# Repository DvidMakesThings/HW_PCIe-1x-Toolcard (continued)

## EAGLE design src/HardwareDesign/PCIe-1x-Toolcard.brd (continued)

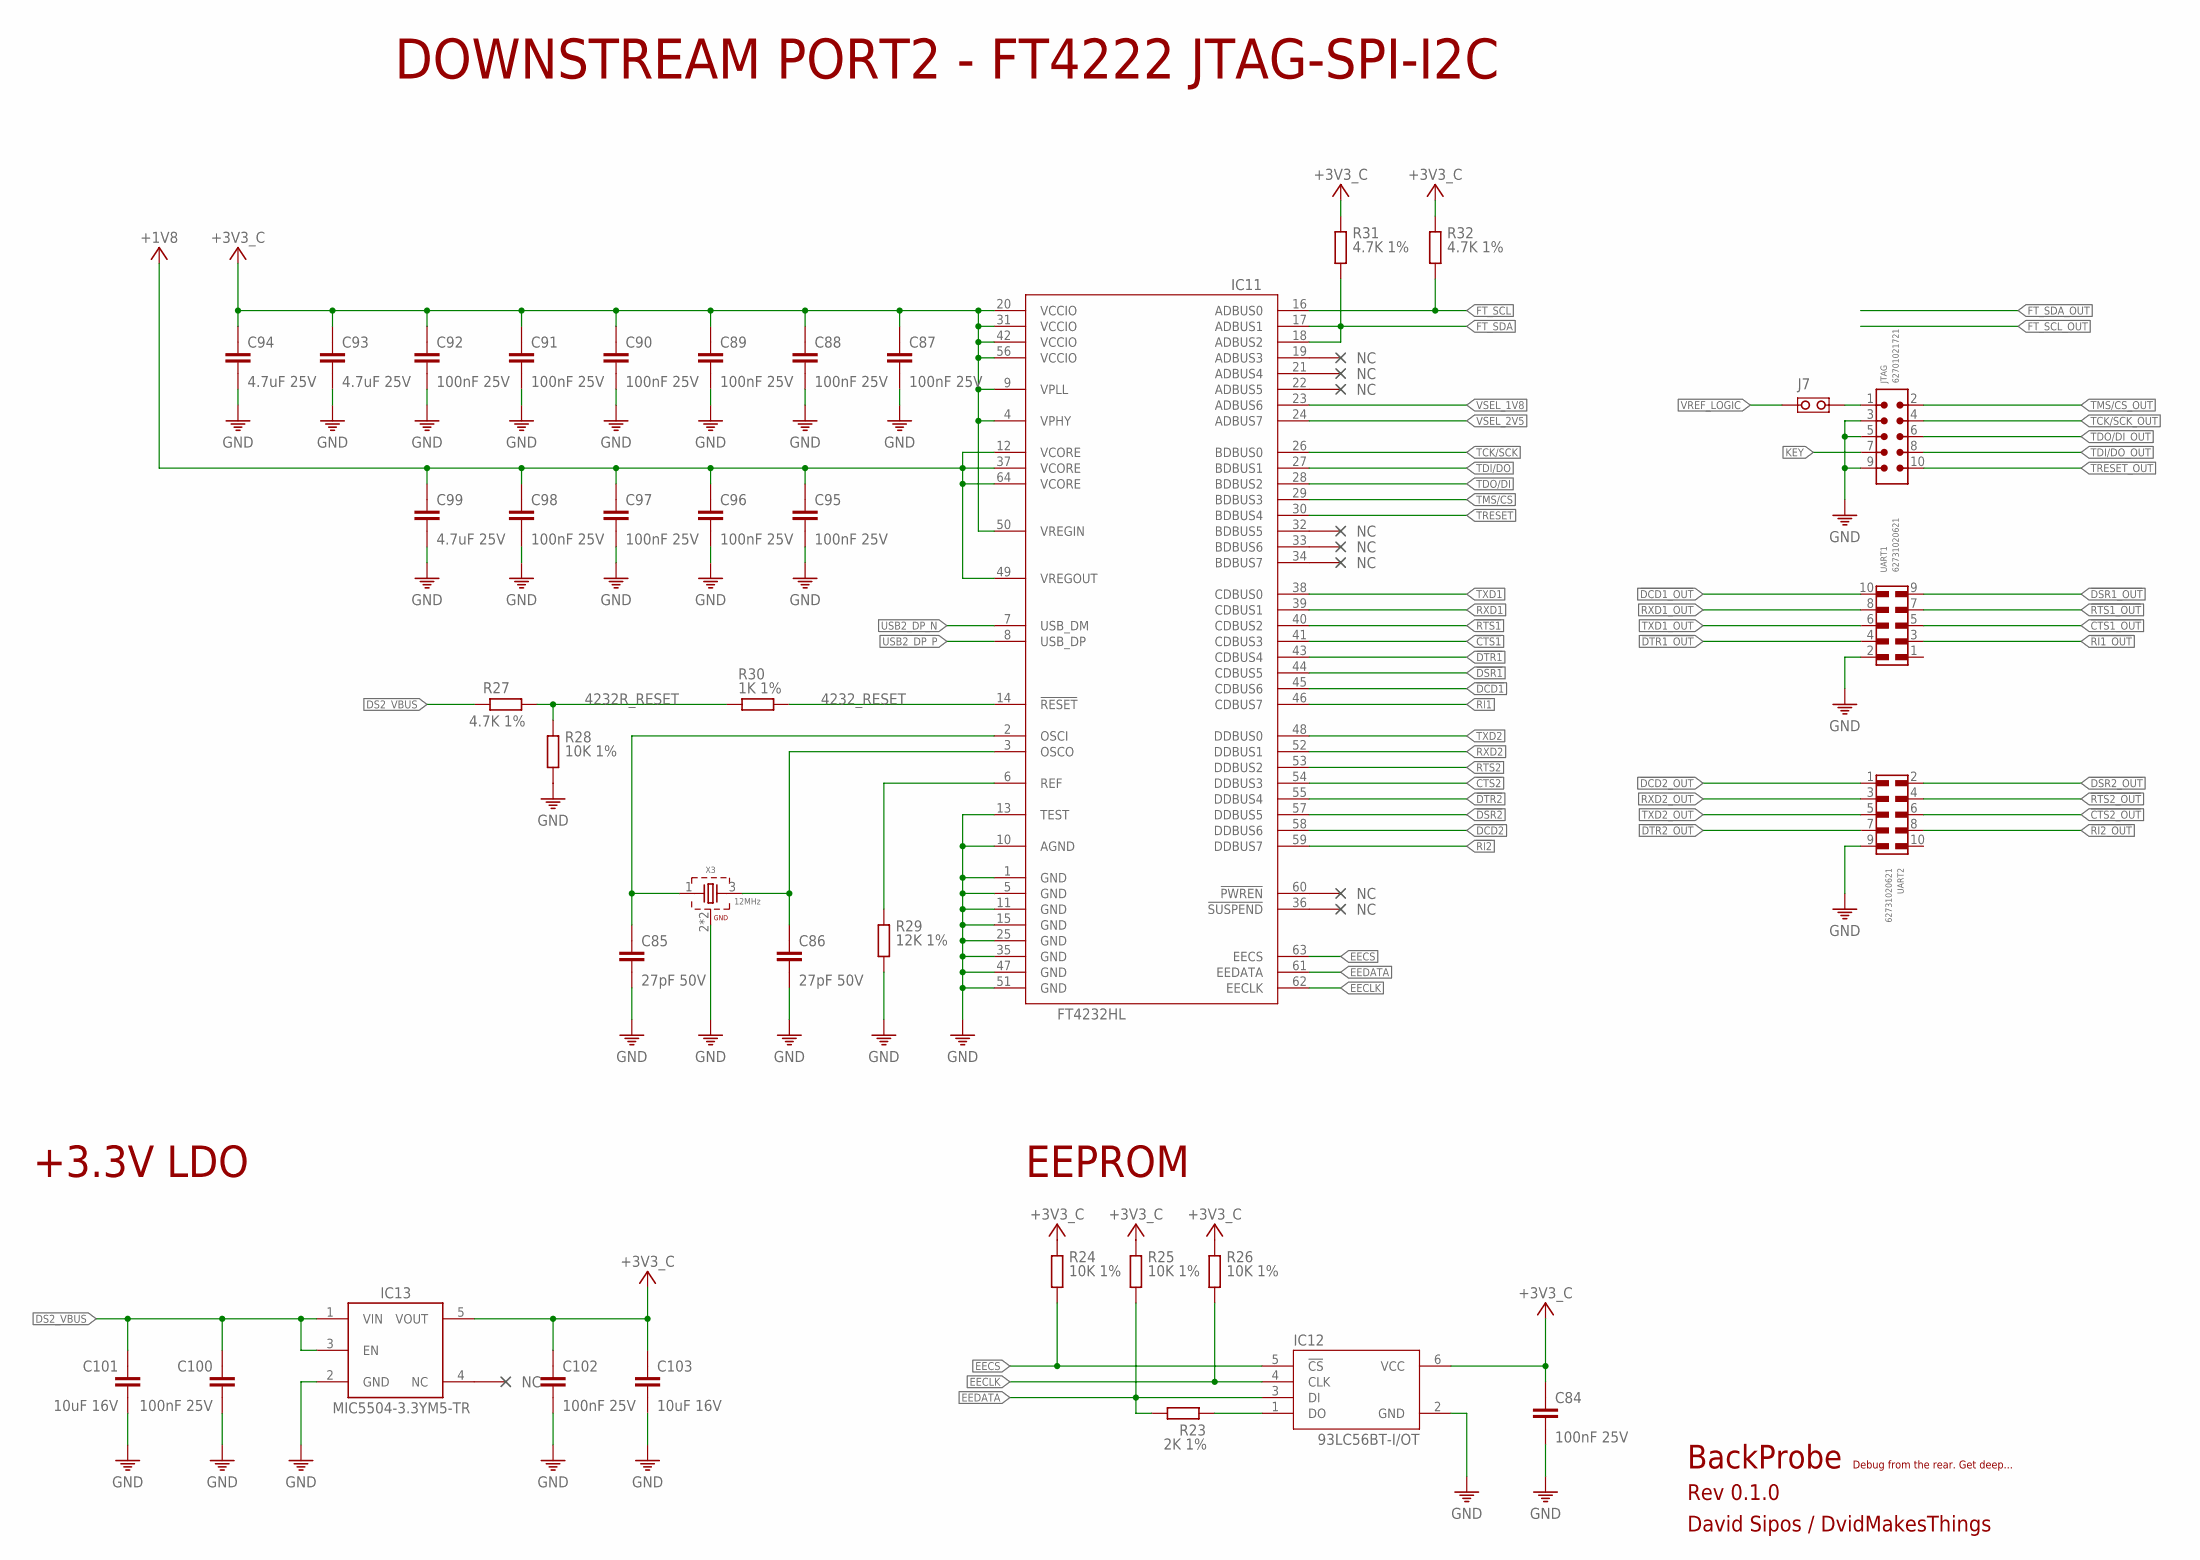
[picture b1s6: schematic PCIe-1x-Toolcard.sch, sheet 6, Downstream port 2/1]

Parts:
C84: 100nF 25V; 0402
C85, C86: 27pF 50V; 0201
C87, C88, C89, C90, C91, C92, C95, C96, C97, C98, C100, C102: 100nF 25V; 0201
C93, C94, C99: 4.7uF 25V; 0402
C101, C103: 10uF 16V; 0603
IC11: FT4232HL; LQFP64-10X10
IC12: 93LC56BT-I/OT; SOT95P280X145-6N
IC13: MIC5504-3.3YM5; SOT23-5
J7: JUMPER-NO; J-0402-NO
JTAG: 62701021721
R23: 2K 1%; 0201
R24, R25, R26, R28: 10K 1%; 0201
R27, R31, R32: 4.7K 1%; 0201
R29: 12K 1%; 0201
R30: 1K 1%; 0201
UART1, UART2: 62731020621
X3: 12MHz; WE-XTAL_CFPX-180

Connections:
4232R_RESET: R27.2, R28.1, R30.1
4232_RESET: IC11.14 (!RESET), R30.2
!CTS1: IC11.41 (CDBUS3); also elsewhere on the board
!CTS1_OUT: UART1.5; also elsewhere on the board
!CTS2: IC11.54 (DDBUS3); also elsewhere on the board
!CTS2_OUT: UART2.6; also elsewhere on the board
!DCD1: IC11.45 (CDBUS6); also elsewhere on the board
!DCD1_OUT: UART1.10; also elsewhere on the board
!DCD2: IC11.58 (DDBUS6); also elsewhere on the board
!DCD2_OUT: UART2.1; also elsewhere on the board
!DSR1: IC11.44 (CDBUS5); also elsewhere on the board
!DSR1_OUT: UART1.9; also elsewhere on the board
!DSR2: IC11.57 (DDBUS5); also elsewhere on the board
!DSR2_OUT: UART2.2; also elsewhere on the board
!DTR1: IC11.43 (CDBUS4); also elsewhere on the board
!DTR1_OUT: UART1.4; also elsewhere on the board
!DTR2: IC11.55 (DDBUS4); also elsewhere on the board
!DTR2_OUT: UART2.7; also elsewhere on the board
!RI1: IC11.46 (CDBUS7); also elsewhere on the board
!RI1_OUT: UART1.3; also elsewhere on the board
!RI2: IC11.59 (DDBUS7); also elsewhere on the board
!RI2_OUT: UART2.8; also elsewhere on the board
!RTS1: IC11.40 (CDBUS2); also elsewhere on the board
!RTS1_OUT: UART1.7; also elsewhere on the board
!RTS2: IC11.53 (DDBUS2); also elsewhere on the board
!RTS2_OUT: UART2.4; also elsewhere on the board
+1V8: C95.1, C96.1, C97.1, C98.1, C99.1, IC11.12 (VCORE), IC11.37 (VCORE), IC11.49 (VREGOUT), IC11.64 (VCORE)
+3V3C: C84.1, C87.1, C88.1, C89.1, C90.1, C91.1, C92.1, C93.1, C94.1, C102.1, C103.1, IC11.4 (VPHY), IC11.9 (VPLL), IC11.20 (VCCIO), IC11.31 (VCCIO), IC11.42 (VCCIO), IC11.50 (VREGIN), IC11.56 (VCCIO), IC12.6 (VCC), IC13.5 (VOUT), R24.1, R25.1, R26.1, R31.1, R32.1; also elsewhere on the board
DS2_VBUS: C100.1, C101.1, IC13.1 (VIN), IC13.3 (EN), R27.1; also elsewhere on the board
EECLK: IC11.62 (EECLK), IC12.4 (CLK), R26.2
EECS: IC11.63 (EECS), IC12.5 (!CS), R24.2
EEDATA: IC11.61 (EEDATA), IC12.3 (DI), R23.2, R25.2
FT_SCL: IC11.16 (ADBUS0), R32.2; also elsewhere on the board
FT_SDA: IC11.17 (ADBUS1), IC11.18 (ADBUS2), R31.2; also elsewhere on the board
GND: C84.2, C85.2, C86.2, C87.2, C88.2, C89.2, C90.2, C91.2, C92.2, C93.2, C94.2, C95.2, C96.2, C97.2, C98.2, C99.2, C100.2, C101.2, C102.2, C103.2, IC11.1 (GND), IC11.5 (GND), IC11.10 (AGND), IC11.11 (GND), IC11.13 (TEST), IC11.15 (GND), IC11.25 (GND), IC11.35 (GND), IC11.47 (GND), IC11.51 (GND), IC12.2 (GND), IC13.2 (GND), JTAG.3, JTAG.5, JTAG.9, R28.2, R29.2, UART1.2, UART2.9, X3.2 (GND), X3.4 (GND); also elsewhere on the board
KEY: JTAG.7
unnamed: IC11.6 (REF), R29.1
unnamed: C85.1, IC11.2 (OSCI), X3.1
unnamed: IC12.1 (DO), R23.1
unnamed: C86.1, IC11.3 (OSCO), X3.3 (2)
unnamed: J7.2, JTAG.1
RXD1: IC11.39 (CDBUS1); also elsewhere on the board
RXD1_OUT: UART1.8; also elsewhere on the board
RXD2: IC11.52 (DDBUS1); also elsewhere on the board
RXD2_OUT: UART2.3; also elsewhere on the board
TCK/SCK: IC11.26 (BDBUS0); also elsewhere on the board
TCK/SCK_OUT: JTAG.4; also elsewhere on the board
TDI/DO: IC11.27 (BDBUS1); also elsewhere on the board
TDI/DO_OUT: JTAG.8; also elsewhere on the board
TDO/DI: IC11.28 (BDBUS2); also elsewhere on the board
TDO/DI_OUT: JTAG.6; also elsewhere on the board
TMS/CS: IC11.29 (BDBUS3); also elsewhere on the board
TMS/CS_OUT: JTAG.2; also elsewhere on the board
TRESET: IC11.30 (BDBUS4)
TRESET_OUT: JTAG.10
TXD1: IC11.38 (CDBUS0); also elsewhere on the board
TXD1_OUT: UART1.6; also elsewhere on the board
TXD2: IC11.48 (DDBUS0); also elsewhere on the board
TXD2_OUT: UART2.5; also elsewhere on the board
USB2_DP_N: IC11.7 (USB_DM); also elsewhere on the board
USB2_DP_P: IC11.8 (USB_DP); also elsewhere on the board
VREF_LOGIC: J7.1; also elsewhere on the board
VSEL_1V8: IC11.23 (ADBUS6); also elsewhere on the board
VSEL_2V5: IC11.24 (ADBUS7); also elsewhere on the board

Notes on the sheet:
BackProbe
Rev 0.1.0
David Sipos / DvidMakesThings
Debug from the rear. Get deep...
DOWNSTREAM PORT2 - FT4222 JTAG-SPI-I2C
+3.3V LDO
EEPROM

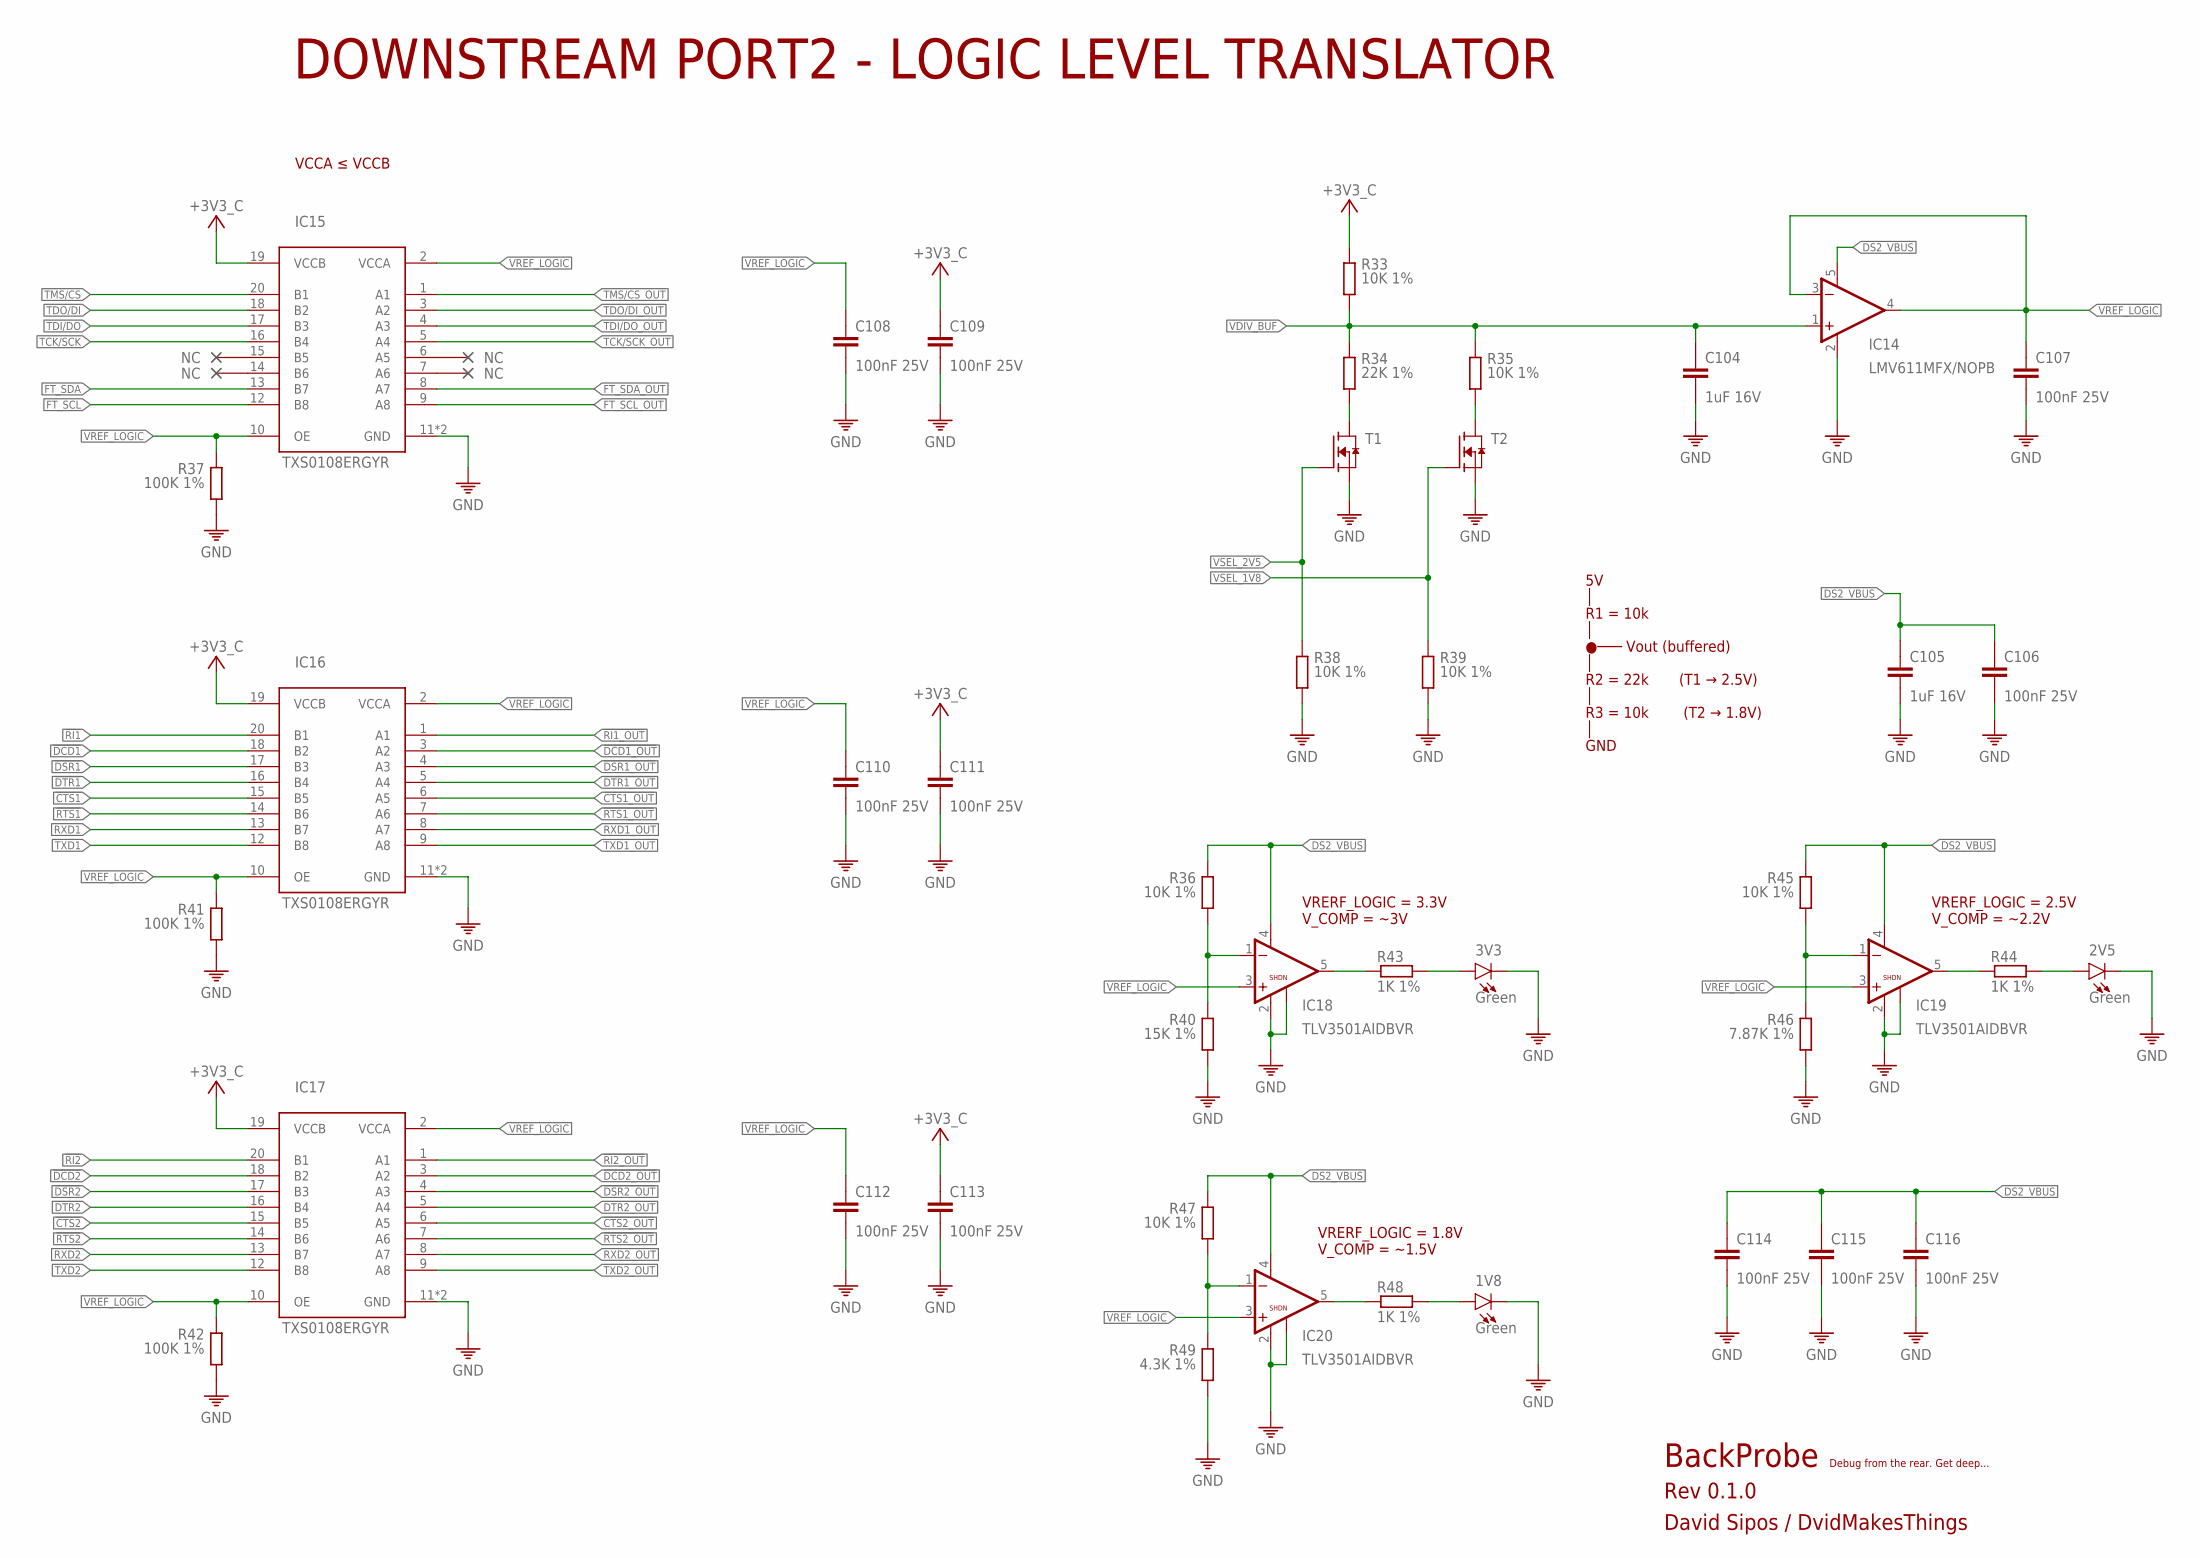
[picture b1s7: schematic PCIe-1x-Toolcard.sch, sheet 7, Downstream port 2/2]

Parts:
1V8, 2V5, 3V3: Green; LED-0603
C104, C105: 1uF 16V; 0201
C106, C107, C108, C109, C110, C111, C112, C113, C114, C115, C116: 100nF 25V; 0201
IC14: LMV611MFX/NOPB; SOT23-5
IC15, IC16, IC17: TXS0108ERGYR; VQFN24
IC18, IC19, IC20: TLV3501AIDBVR; SOT95P280X145-6N
R33, R35, R38, R39: 10K 1%; 0402
R34: 22K 1%; 0402
R36, R45, R47: 10K 1%; 0201
R37, R41, R42: 100K 1%; 0201
R40: 15K 1%; 0201
R43, R44, R48: 1K 1%; 0603
R46: 7.87K 1%; 0201
R49: 4.3K 1%; 0201
T1, T2: BSS138; SOT23

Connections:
!CTS1: IC16.15 (B5); also elsewhere on the board
!CTS1_OUT: IC16.6 (A5); also elsewhere on the board
!CTS2: IC17.15 (B5); also elsewhere on the board
!CTS2_OUT: IC17.6 (A5); also elsewhere on the board
!DCD1: IC16.18 (B2); also elsewhere on the board
!DCD1_OUT: IC16.3 (A2); also elsewhere on the board
!DCD2: IC17.18 (B2); also elsewhere on the board
!DCD2_OUT: IC17.3 (A2); also elsewhere on the board
!DSR1: IC16.17 (B3); also elsewhere on the board
!DSR1_OUT: IC16.4 (A3); also elsewhere on the board
!DSR2: IC17.17 (B3); also elsewhere on the board
!DSR2_OUT: IC17.4 (A3); also elsewhere on the board
!DTR1: IC16.16 (B4); also elsewhere on the board
!DTR1_OUT: IC16.5 (A4); also elsewhere on the board
!DTR2: IC17.16 (B4); also elsewhere on the board
!DTR2_OUT: IC17.5 (A4); also elsewhere on the board
!RI1: IC16.20 (B1); also elsewhere on the board
!RI1_OUT: IC16.1 (A1); also elsewhere on the board
!RI2: IC17.20 (B1); also elsewhere on the board
!RI2_OUT: IC17.1 (A1); also elsewhere on the board
!RTS1: IC16.14 (B6); also elsewhere on the board
!RTS1_OUT: IC16.7 (A6); also elsewhere on the board
!RTS2: IC17.14 (B6); also elsewhere on the board
!RTS2_OUT: IC17.7 (A6); also elsewhere on the board
+3V3C: C109.1, C111.1, C113.1, IC15.19 (VCCB), IC16.19 (VCCB), IC17.19 (VCCB), R33.1; also elsewhere on the board
COMP18_O: IC20.5 (OUT), R48.1
COMP25_O: IC19.5 (OUT), R44.1
COMP33_O: IC18.5 (OUT), R43.1
D25: R35.2, T2.3 (D)
D33: R34.2, T1.3 (D)
DS2_VBUS: C105.1, C106.1, C114.1, C115.1, C116.1, IC14.5 (V+), IC18.4 (V+), IC19.4 (V+), IC20.4 (V+), R36.1, R45.1, R47.1; also elsewhere on the board
FT_SCL: IC15.12 (B8); also elsewhere on the board
FT_SCL_OUT: IC15.9 (A8)
FT_SDA: IC15.13 (B7); also elsewhere on the board
FT_SDA_OUT: IC15.8 (A7)
GND: 1V8.C, 2V5.C, 3V3.C, C104.2, C105.2, C106.2, C107.2, C108.2, C109.2, C110.2, C111.2, C112.2, C113.2, C114.2, C115.2, C116.2, IC14.2 (V-), IC15.11 (GND), IC15.PAD (GND), IC16.11 (GND), IC16.PAD (GND), IC17.11 (GND), IC17.PAD (GND), IC18.2 (V-), IC18.6 (SHDN), IC19.2 (V-), IC19.6 (SHDN), IC20.2 (V-), IC20.6 (SHDN), R37.2, R38.2, R39.2, R40.2, R41.2, R42.2, R46.2, R49.2, T1.2 (S), T2.2 (S); also elsewhere on the board
unnamed: 3V3.A, R43.2
unnamed: 2V5.A, R44.2
unnamed: 1V8.A, R48.2
RXD1: IC16.13 (B7); also elsewhere on the board
RXD1_OUT: IC16.8 (A7); also elsewhere on the board
RXD2: IC17.13 (B7); also elsewhere on the board
RXD2_OUT: IC17.8 (A7); also elsewhere on the board
TCK/SCK: IC15.16 (B4); also elsewhere on the board
TCK/SCK_OUT: IC15.5 (A4); also elsewhere on the board
TDI/DO: IC15.17 (B3); also elsewhere on the board
TDI/DO_OUT: IC15.4 (A3); also elsewhere on the board
TDO/DI: IC15.18 (B2); also elsewhere on the board
TDO/DI_OUT: IC15.3 (A2); also elsewhere on the board
TMS/CS: IC15.20 (B1); also elsewhere on the board
TMS/CS_OUT: IC15.1 (A1); also elsewhere on the board
TXD1: IC16.12 (B8); also elsewhere on the board
TXD1_OUT: IC16.9 (A8); also elsewhere on the board
TXD2: IC17.12 (B8); also elsewhere on the board
TXD2_OUT: IC17.9 (A8); also elsewhere on the board
VDIV_BUF: C104.1, IC14.1 (+IN), R33.2, R34.1, R35.1
VREF_LOGIC: C107.1, C108.1, C110.1, C112.1, IC14.3 (-IN), IC14.4 (OUT), IC15.2 (VCCA), IC15.10 (OE), IC16.2 (VCCA), IC16.10 (OE), IC17.2 (VCCA), IC17.10 (OE), IC18.3 (+IN), IC19.3 (+IN), IC20.3 (+IN), R37.1, R41.1, R42.1; also elsewhere on the board
VSEL_1V8: R39.1, T2.1 (G); also elsewhere on the board
VSEL_2V5: R38.1, T1.1 (G); also elsewhere on the board
V_COMP18: IC20.1 (-IN), R47.2, R49.1
V_COMP25: IC19.1 (-IN), R45.2, R46.1
V_COMP33: IC18.1 (-IN), R36.2, R40.1

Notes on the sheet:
BackProbe
Rev 0.1.0
David Sipos / DvidMakesThings
Debug from the rear. Get deep...
DOWNSTREAM PORT2 - LOGIC LEVEL TRANSLATOR
5V │ R1 = 10k │ ●─── Vout (buffered) │ R2 = 22k (T1 → 2.5V) │ R3 = 10k (T2 → 1.8V) │ GND
VCCA ≤ VCCB
VRERF_LOGIC = 3.3V V_COMP = ~3V
VRERF_LOGIC = 2.5V V_COMP = ~2.2V
VRERF_LOGIC = 1.8V V_COMP = ~1.5V

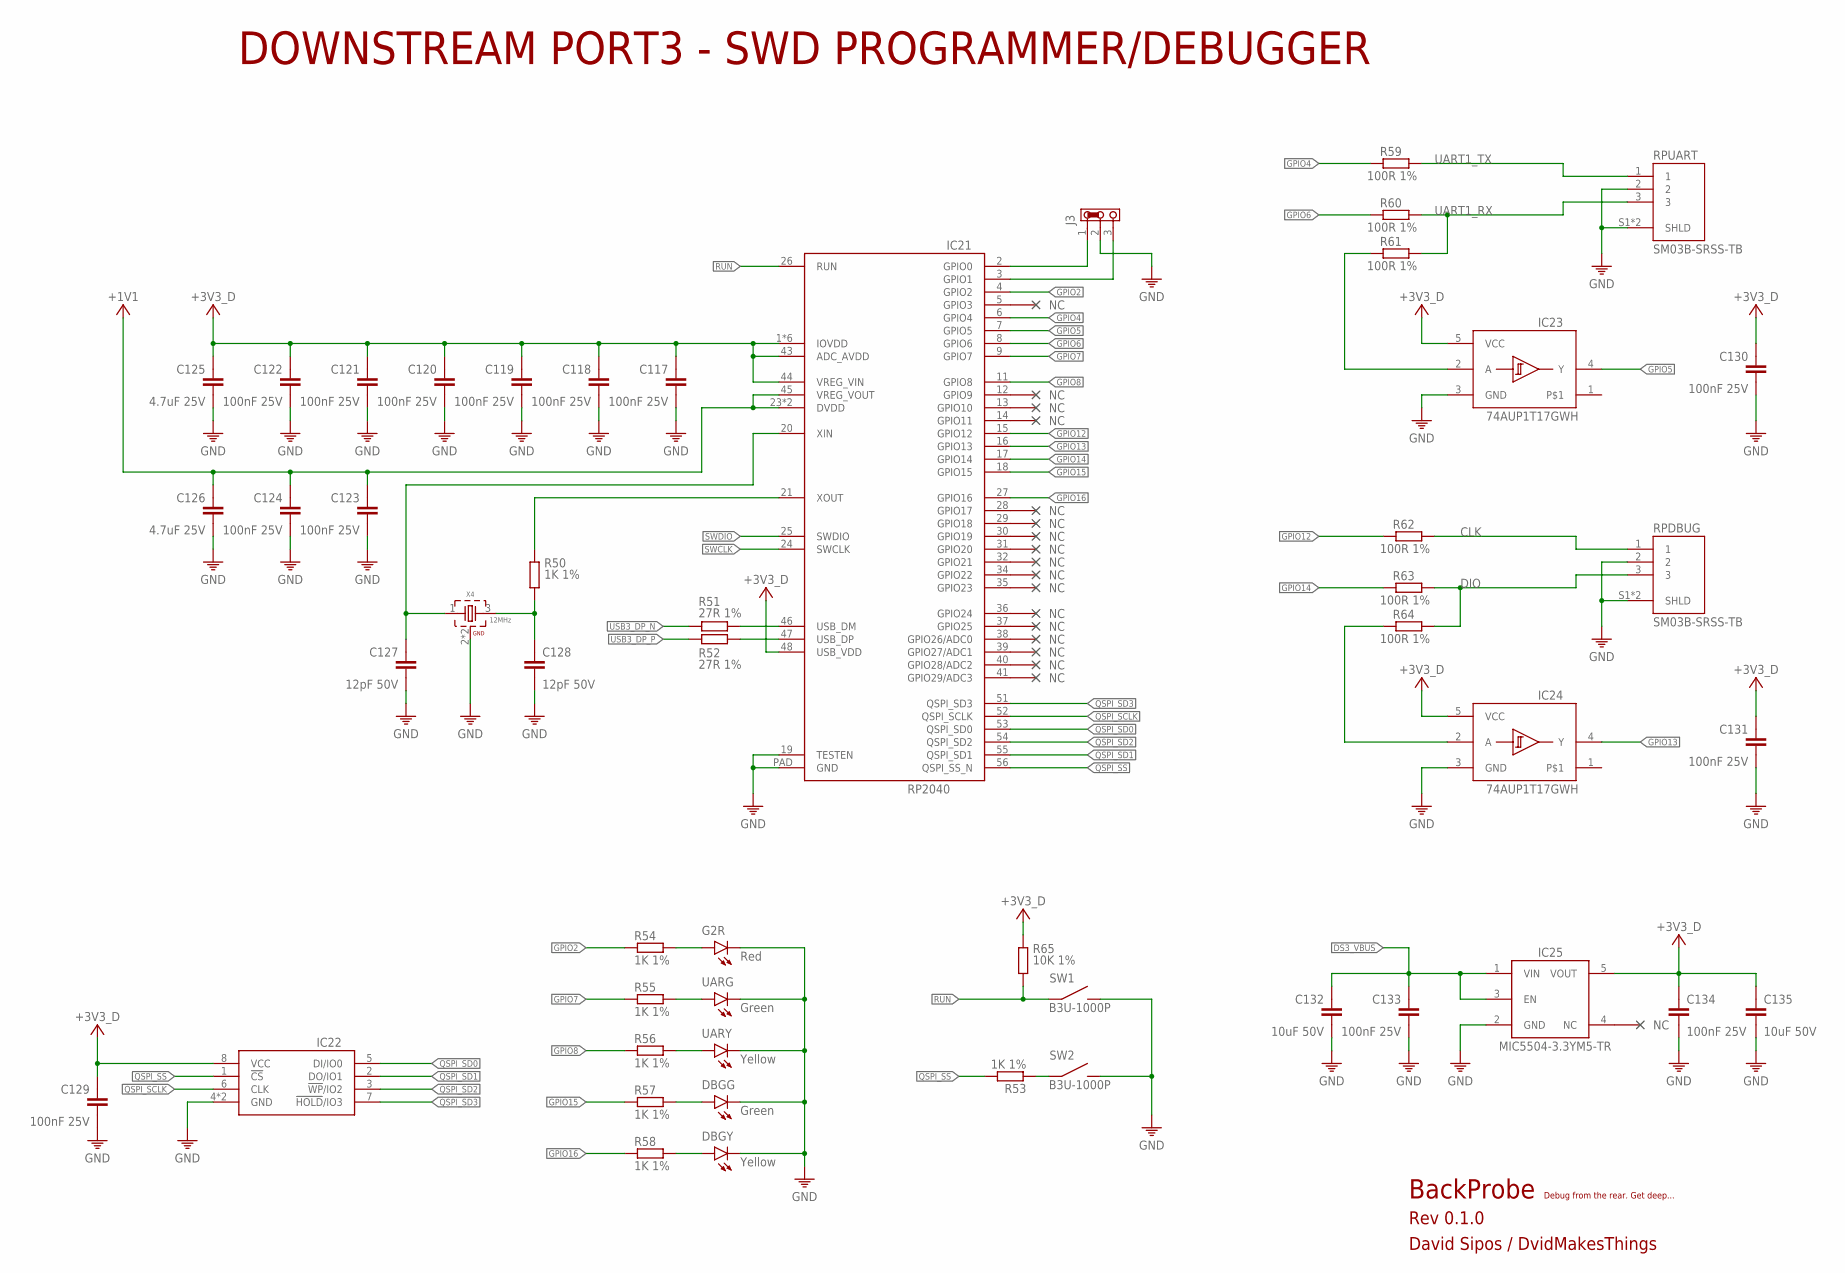
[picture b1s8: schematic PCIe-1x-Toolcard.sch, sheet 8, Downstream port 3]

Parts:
C117, C118, C119, C120, C121, C122, C123, C124, C129, C130, C131, C133, C134: 100nF 25V; 0201
C125, C126: 4.7uF 25V; 0402
C127, C128: 12pF 50V; 0201
C132, C135: 10uF 50V; 0805
DBGG: Green; LED-0603
DBGY: Yellow; LED-0603
G2R: Red; LED-0603
IC21: RP2040; QFN56
IC22: W25Q128JVP; SON127P600X500X75-8N
IC23, IC24: 74AUP1T17GWH; SOT353-1
IC25: MIC5504-3.3YM5; SOT23-5
J3: JUMPER-3
R50, R53: 1K 1%; 0201
R51, R52: 27R 1%; 0201
R54, R55, R56, R57, R58: 1K 1%; 0402
R59, R60, R61, R62, R63, R64: 100R 1%; 0201
R65: 10K 1%; 0201
RPDBUG: SM03B-SRSS-TB
RPUART: SM03B-SRSS-TB
SW1, SW2: B3U-1000P
UARG: Green; LED-0603
UARY: Yellow; LED-0603
X4: 12MHz; WE-XTAL_CFPX-180

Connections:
+1V1: C123.1, C124.1, C126.1, IC21.23 (DVDD), IC21.45 (VREG_VOUT), IC21.50 (DVDD)
+3V3D: C117.1, C118.1, C119.1, C120.1, C121.1, C122.1, C125.1, C129.1, C130.1, C131.1, C134.1, C135.1, IC21.1 (IOVDD), IC21.10 (IOVDD), IC21.22 (IOVDD), IC21.33 (IOVDD), IC21.42 (IOVDD), IC21.43 (ADC_AVDD), IC21.44 (VREG_VIN), IC21.48 (USB_VDD), IC21.49 (IOVDD), IC22.8 (VCC), IC23.5 (VCC), IC24.5 (VCC), IC25.5 (VOUT), R65.1
BOOT: R53.1, SW2.1
CLK: R62.2, RPDBUG.1
DIO: R63.2, R64.2, RPDBUG.3
DS3_VBUS: C132.1, C133.1, IC25.1 (VIN), IC25.3 (EN); also elsewhere on the board
GND: C117.2, C118.2, C119.2, C120.2, C121.2, C122.2, C123.2, C124.2, C125.2, C126.2, C127.2, C128.2, C129.2, C130.2, C131.2, C132.2, C133.2, C134.2, C135.2, DBGG.C, DBGY.C, G2R.C, IC21.19 (TESTEN), IC21.PAD (GND), IC22.4 (GND), IC22.PAD (GND), IC23.3 (GND), IC24.3 (GND), IC25.2 (GND), J3.2, RPDBUG.2, RPDBUG.S1 (SHLD), RPDBUG.S2 (SHLD), RPUART.2, RPUART.S1 (SHLD), RPUART.S2 (SHLD), SW1.2, SW2.2, UARG.C, UARY.C, X4.2 (GND), X4.4 (GND); also elsewhere on the board
GPIO2: IC21.4 (GPIO2), R54.1
GPIO4: IC21.6 (GPIO4), R59.1
GPIO5: IC21.7 (GPIO5), IC23.4 (Y)
GPIO6: IC21.8 (GPIO6), R60.1
GPIO7: IC21.9 (GPIO7), R55.1
GPIO8: IC21.11 (GPIO8), R56.1
GPIO12: IC21.15 (GPIO12), R62.1
GPIO13: IC21.16 (GPIO13), IC24.4 (Y)
GPIO14: IC21.17 (GPIO14), R63.1
GPIO15: IC21.18 (GPIO15), R57.1
GPIO16: IC21.27 (GPIO16), R58.1
unnamed: IC21.2 (GPIO0), J3.1
unnamed: IC21.3 (GPIO1), J3.3
unnamed: C127.1, IC21.20 (XIN), X4.1
unnamed: C128.1, R50.2, X4.3 (2)
unnamed: IC21.21 (XOUT), R50.1
unnamed: G2R.A, R54.2
unnamed: DBGG.A, R57.2
unnamed: DBGY.A, R58.2
unnamed: R56.2, UARY.A
unnamed: R55.2, UARG.A
unnamed: IC24.2 (A), R64.1
unnamed: IC23.2 (A), R61.1
QSPI_SCLK: IC21.52 (QSPI_SCLK), IC22.6 (CLK)
QSPI_SD0: IC21.53 (QSPI_SD0), IC22.5 (DI/IO0)
QSPI_SD1: IC21.55 (QSPI_SD1), IC22.2 (DO/IO1)
QSPI_SD2: IC21.54 (QSPI_SD2), IC22.3 (!WP!/IO2)
QSPI_SD3: IC21.51 (QSPI_SD3), IC22.7 (!HOLD!/IO3)
QSPI_SS: IC21.56 (QSPI_SS_N), IC22.1 (!CS), R53.2
RUN: IC21.26 (RUN), R65.2, SW1.1
SWCLK: IC21.24 (SWCLK)
SWDIO: IC21.25 (SWDIO)
UART1_RX: R60.2, R61.2, RPUART.3
UART1_TX: R59.2, RPUART.1
USB3_DP_N: R51.1; also elsewhere on the board
USB3_DP_P: R52.2; also elsewhere on the board
USB_PID_N: IC21.46 (USB_DM), R51.2
USB_PID_P: IC21.47 (USB_DP), R52.1

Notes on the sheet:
BackProbe
Rev 0.1.0
David Sipos / DvidMakesThings
Debug from the rear. Get deep...
DOWNSTREAM PORT3 - SWD PROGRAMMER/DEBUGGER

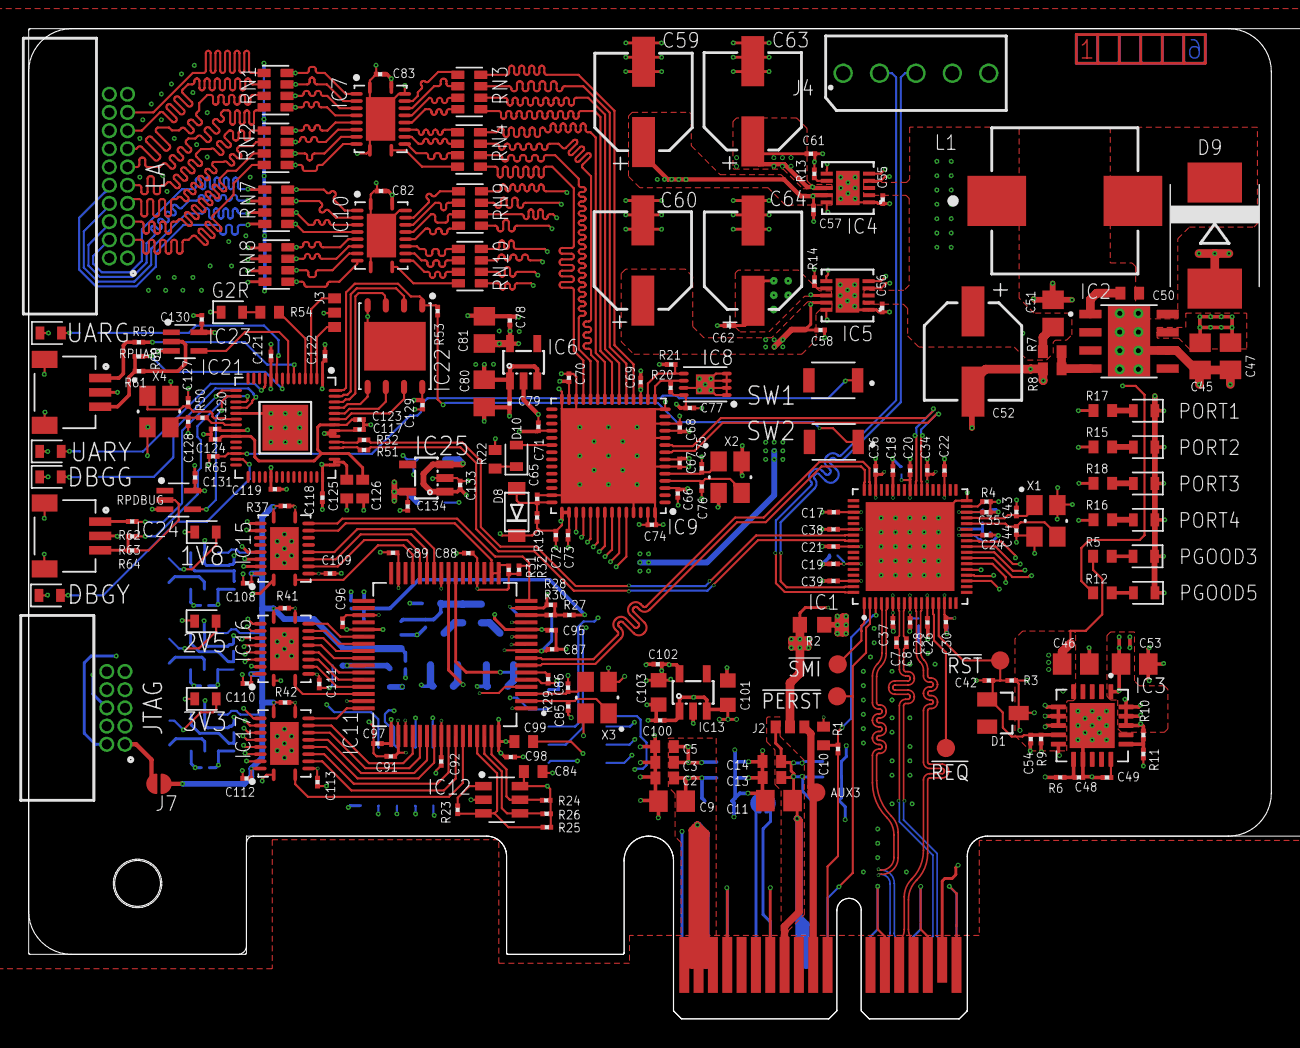
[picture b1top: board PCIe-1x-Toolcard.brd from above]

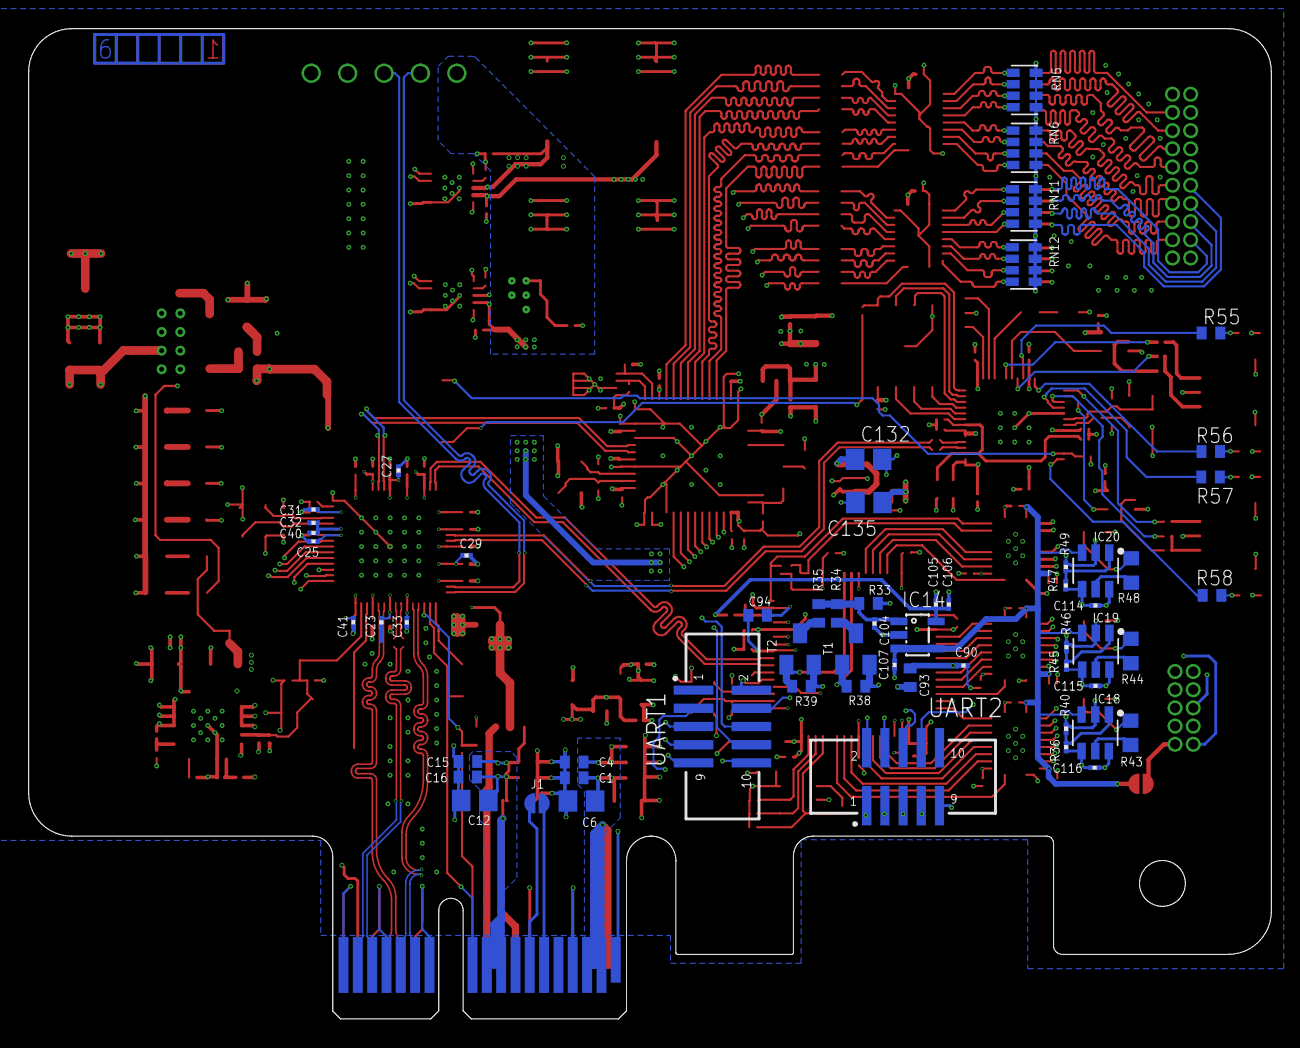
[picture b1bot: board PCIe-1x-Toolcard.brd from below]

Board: 6 copper layers, 86.7 x 69.1 mm, 281 parts (58 on the bottom side), 242 nets.

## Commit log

2025-06-02 start implementation and design
2025-06-06 Add JLC06161H-3313A 6-layer stackup configuration with detailed specifications
    - Introduced a new XML file for the JLC06161H-3313A PCB stackup.
    - Included comprehensive descriptions of layer stackup, materials, and controlled impedance configurations.
    - Defined various manufacturing parameters such as copper weights, isolation thicknesses, and pad dimensions.
    - Specified controlled impedance configurations for different signal layers.
